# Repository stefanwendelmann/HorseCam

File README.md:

# HorseCam
A A6C driven Project, wich is used to read SMS and Send a Picture taken by the A6C Camera to a HTTP POST Server, to monitor the horse of my gf.

# Communication Model

# BOM
* A6C
* Arduino Nano v3 (incl. USB Cable for programming)
* SMA Antenna
* maybe SMA extension
* N-Channel Mosfet like 3055 (i took "2N7002 702 7002 SMD SOT-23 N -Kanal- 60V 115mA MosFET")
* SIM Card (i got mine from Netzclub)
* ~~Step Down modul (low power consumption) i took a LM2596 (assabling instructions will follow)~~
* 5V Powerbank and Micro USB Cable
* i will add more soon

# Links
## Donate we need a PCB Milling CNC for our fablab

### Raymond Tunning's Blog
https://raymondtunning.wordpress.com/tag/a6c/
### AI Thinker Wiki
http://wiki.ai-thinker.com/gprs
### Google Translator
https://translate.google.de/m/translate
### YouTube Links
https://www.youtube.com/watch?v=4xaPfY7r8qU

# Resources
Nano Pinout
http://www.pighixxx.com/test/wp-content/uploads/2014/11/nano.png

# PCB Prototyping
http://pcbshopper.com/

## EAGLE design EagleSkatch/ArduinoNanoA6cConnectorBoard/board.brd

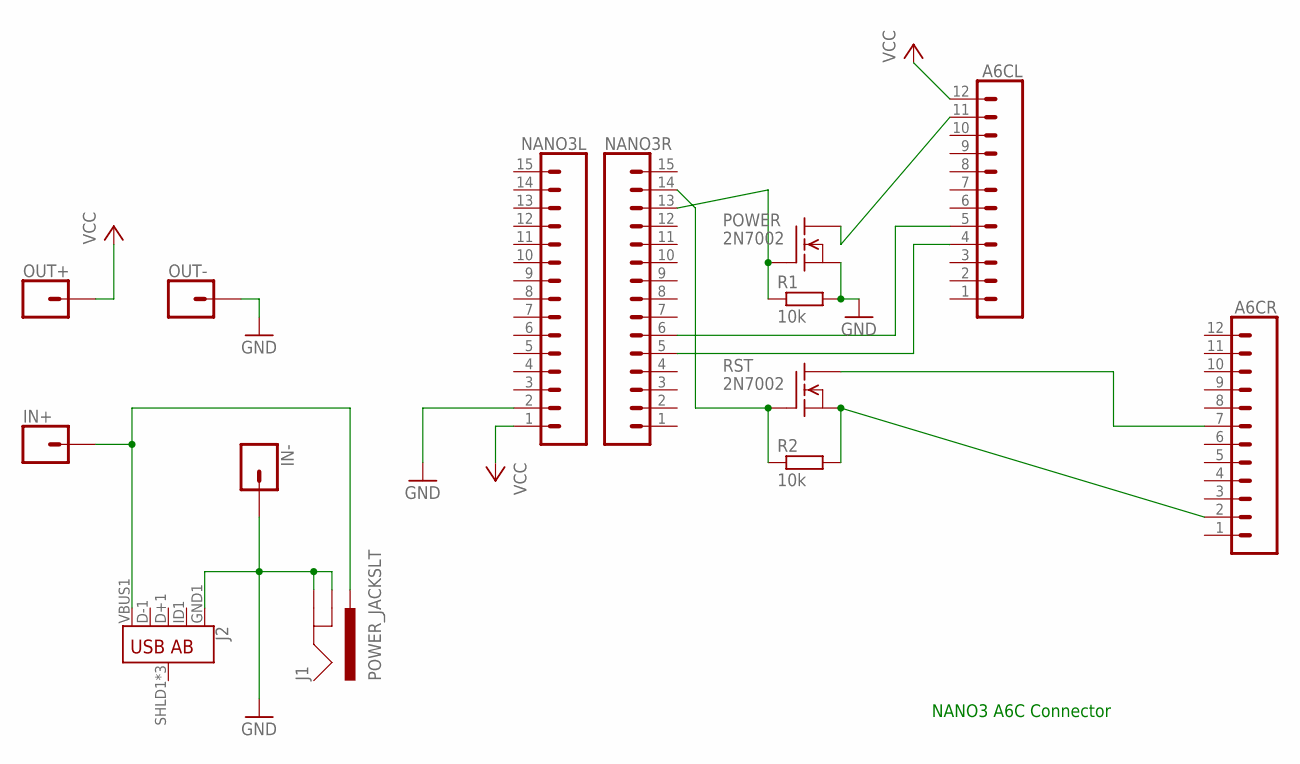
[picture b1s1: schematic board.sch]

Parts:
A6CL, A6CR: CONN_12; 1X12
IN+: CONN_01; 1X01
IN-: CONN_01; 1X01
J1: POWER_JACKSLT; POWER_JACK_SLOT
J2: USB_AB_SMT; USB-AB-MICRO-SMD
NANO3L, NANO3R: CONN_15; 1X15
OUT+: CONN_01; 1X01
OUT-: CONN_01; 1X01
POWER: 2N7002; SOT23
R1, R2: 10k; R0402
RST: 2N7002; SOT23

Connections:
GND: IN-.1, J1.GND@1 (GNDBREAK), J1.GND@2 (GND), J2.GND1 (GND), NANO3L.2, OUT-.1, POWER.2 (S), R1.2
unnamed: IN+.1, J1.PWR, J2.VBUS1 (VBUS)
unnamed: A6CR.7, RST.3 (D)
unnamed: NANO3R.13, POWER.1 (G), R1.1
unnamed: NANO3R.14, R2.1, RST.1 (G)
unnamed: A6CR.2, R2.2, RST.2 (S)
unnamed: A6CL.11, POWER.3 (D)
unnamed: A6CL.4, NANO3R.5
unnamed: A6CL.5, NANO3R.6
VCC: A6CL.12, NANO3L.1, OUT+.1

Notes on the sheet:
NANO3 A6C Connector

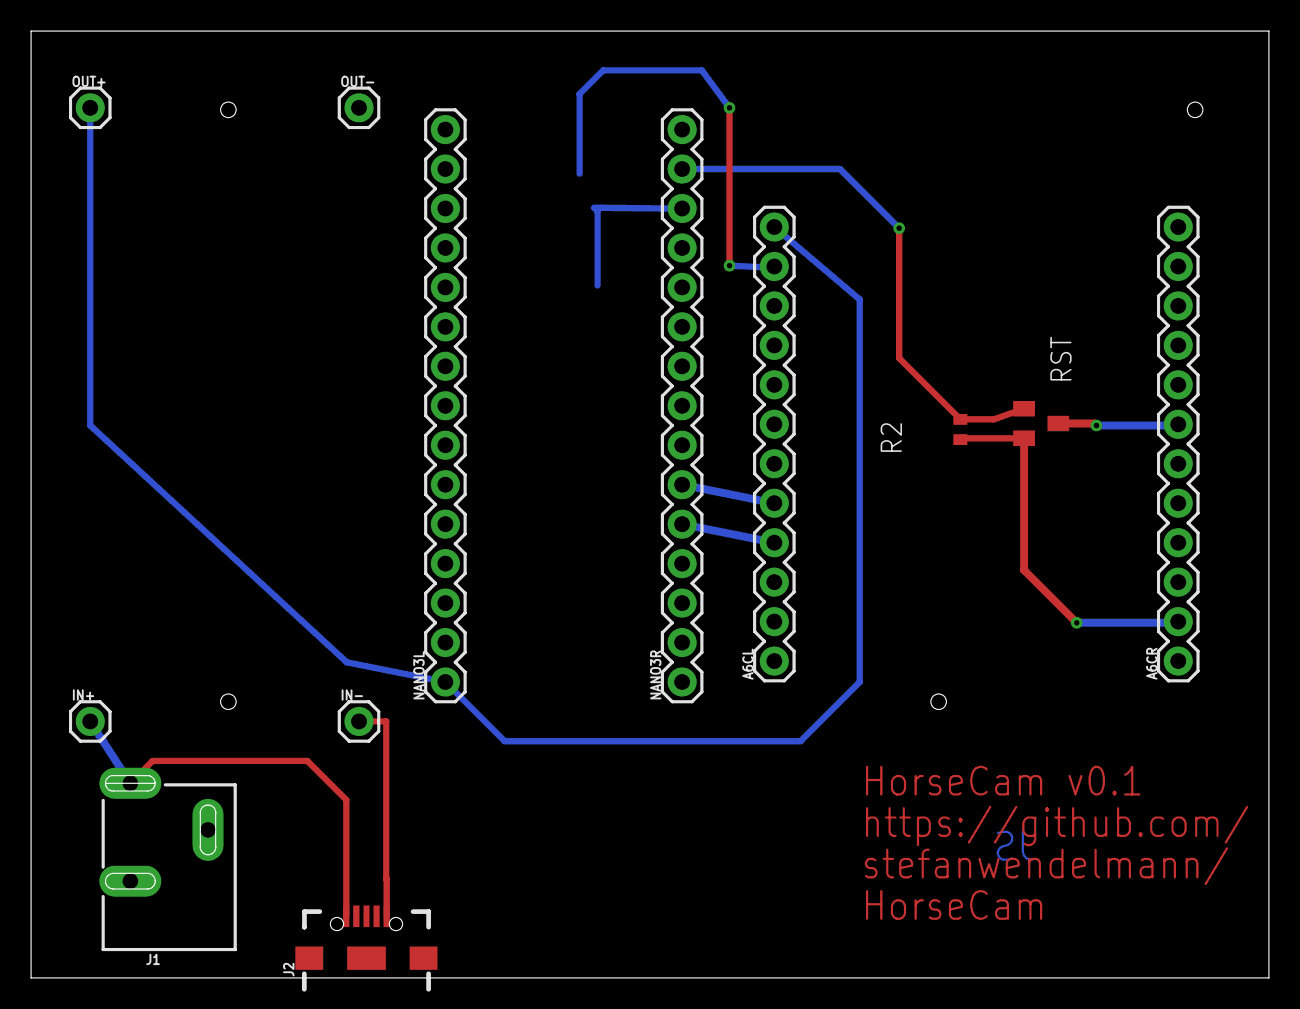
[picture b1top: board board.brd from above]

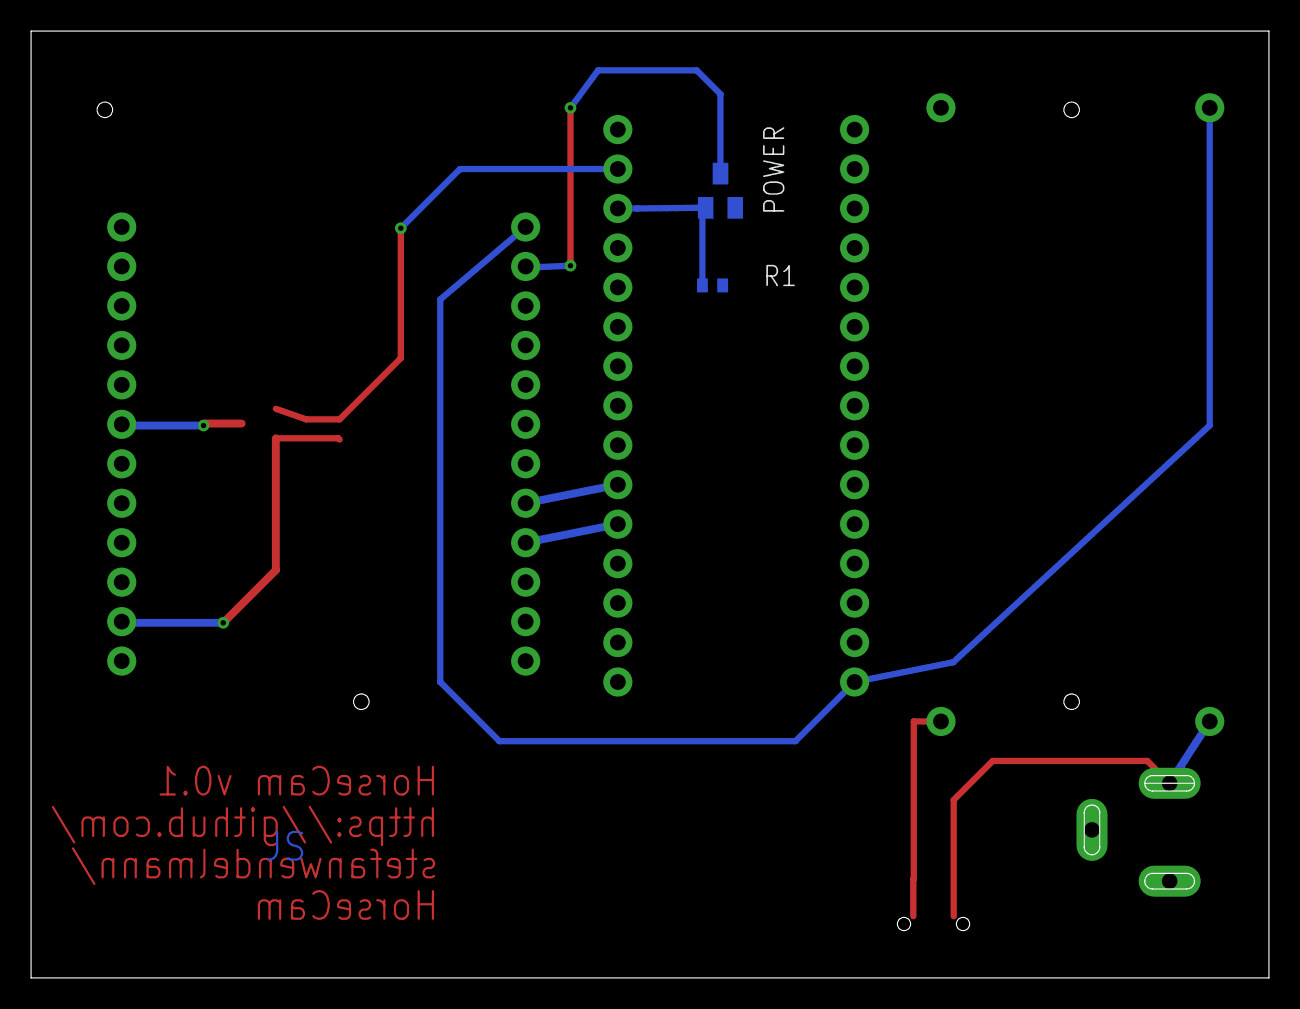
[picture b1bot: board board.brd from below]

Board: 2 copper layers, 79.7 x 61.0 mm, 14 parts (2 on the bottom side), 10 nets.

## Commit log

2017-05-12 Added useful links
2017-05-12 A6C Documents
    Added the A6C Documents from the AI Thinker Wiki
2017-05-12 Added Communication.xml
2017-05-12 First Draft
2017-05-12 Added Communication.png
2017-05-12 Updatet Communication Model
2017-05-12 Added the Adruino for the Logic
2017-05-12 First test pictures with A6C
2017-05-12 Start to translation
2017-05-12 Kamera Übersetzung de-de
2017-05-12 Tabellenanpassungen
2017-05-18 Mixed
    Arduino first sketch and pinout, Server test
2017-05-18 BOM
    Edit BOM
2017-05-20 Added PAP
2017-05-20 Added PAP.png
2017-05-20 Added Some electronic stuff
    Started to draw a eagle PCB for connection
    N Chanal Mosfet discription and example
2017-05-21 Board Design
2017-05-22 Boarddesign finnished
    Finished Board design and send it to seed studio
2017-05-22 Started to Setup the Code
    Code Setup für Arduino, testet some functions of the A6C SMS SIM Storage
    modes CNMI
2017-05-24 Added Donate Link
2017-05-24 Edit Dontae
2017-05-24 Edit Donate
2017-05-24 Donate Button
2017-05-24 edit Readme
    Clean Readme & added CNC icon
2017-05-24 Readmd correction
    Correct the list and icon
2019-08-02 PHP Save Serverside Script

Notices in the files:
parts and their libraries:
SparkFun-Connectors: Licensing: Creative Commons ShareAlike 4.0 International - https://creativecommons.org/licenses/by-sa/4.0
